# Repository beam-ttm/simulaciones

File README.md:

# Simulaciones Electromagnéticas — Proyecto CubeSat BEAM (UNLaM)

Repositorio oficial de simulaciones electromagnéticas **Full-Wave MoM (Sonnet Software 19.54)** y codiseño RF/PCB para el subsistema **ADS-B (`1090.0 MHz`, polarización circular derecha RHCP)** del CubeSat **BEAM** (Universidad Nacional de La Matanza).

---

## Estructura del Repositorio

- **[`diseno_final_patch_1090/`](diseno_final_patch_1090/)**: **Diseño final validado (Sonnet + KiCad + Imágenes para Stand)**
  - [`diseno_final_patch_1090/sonnet/`](diseno_final_patch_1090/sonnet/): Proyecto final de Sonnet (`patch_completa_jp3_gcpw_CP_1090.sonx`), parámetros Touchstone de 181 puntos (`1.000 – 1.180 GHz`, paso `1 MHz`), corrientes superficiales MoM (`sondata/.../jxy/current_1.sid`), verificación de 2 puertos de la transición coplanar-vía (`transicion_jp3_gcpw_via_50ohm.sonx`) y plantillas gráficas (`.sgrx`, `.sptx`).
  - [`diseno_final_patch_1090/kicad/`](diseno_final_patch_1090/kicad/): Proyecto de KiCad (`ads-b.kicad_pcb`, `ads-b.kicad_pro`, `ads-b.kicad_sch`, `skillkicad.md`) sincronizado 1:1 con el modelo electromagnético de Sonnet y verificado con `0` errores DRC de cobre/bordes.
  - [`diseno_final_patch_1090/imagenes_stand/`](diseno_final_patch_1090/imagenes_stand/): Infografías en alta resolución (`300 DPI` / 4K), diagramas de corriente superficial MoM, patrones de radiación 3D/Polar/2D y renders 3D raytraced listos para exhibición en stand.
- **[`sonnet/adsb_patch/`](sonnet/adsb_patch/)**: Historial de barridos paramétricos, scripts de automatización, síntesis del stackup `JLC04161H-2116` y estudios comparativos previos.

---

## Resumen de Resultados del Diseño Final (`1090.0 MHz`)

| Parámetro | Valor Simulado (Full-Wave MoM) | Especificación / Objetivo |
| :--- | :--- | :--- |
| **Frecuencia central de operación** | **`1090.0 MHz`** (mínimo en `1087.0 MHz`) | `1090.0 MHz` (ADS-B Mode-S) |
| **Pérdida de retorno $|S_{11}|$ desde `JP3`** | **`-27.62 dB`** @ `1090 MHz` (`-32.49 dB` @ `1087 MHz`) | $< -15	ext{ dB}$ |
| **Impedancia de entrada $Z_{\text{in, JP3}}$** | **`46.5 + j2.5 Ω`** @ `1090 MHz` (`49.0 + j2.1 Ω` @ `1087 MHz`) | $50\ \Omega$ |
| **Ancho de banda a `-10 dB` ($	ext{VSWR} < 2:1$)** | **`34.0 MHz`** (`1074.0 – 1108.0 MHz`) | $\ge 20	ext{ MHz}$ |
| **Ganancia Circular Derecha (`RHCP`, `E-RHP`)** | **`+9.66 dBiC`** ($\theta = 0^\circ$) | $> +6.0	ext{ dBiC}$ |
| **Rechazo Cross-Polar (`LHCP`, `E-LHP`)** | **`-5.95 dBiC`** (`15.61 dB` de aislamiento RHCP/LHCP) | $> 15	ext{ dB}$ |
| **Relación Axial (`Axial Ratio`, AR)** | **`2.90 dB`** ($\theta = 0^\circ$) | $\le 3.0	ext{ dB}$ (Polarización Circular) |
| **Ancho de haz de media potencia (`HPBW` a `-3 dB`)** | **`97.3° × 101.5°`** (`~99.4°` promedio) | Cobertura hemisférica ancha LEO |
| **Pérdida de inserción transición `JP3 -> GCPW -> Vía`** | **`|S21| = -0.049 dB`** (`|S11| = -26.85 dB`) | $< 0.1	ext{ dB}$ |

---

## Galería Visual para Stand

### 1. Excitación de Modos en Cuadratura RHCP y Patrón Cartesiano 2D

### 2. Modelo 3D Raytraced de la Placa CubeSat PC/104 (`F.Cu` Parche RHCP + `B.Cu` Front-End RF)

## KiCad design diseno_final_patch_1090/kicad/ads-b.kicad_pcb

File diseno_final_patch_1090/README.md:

# Simulaciones Electromagnéticas — Proyecto CubeSat BEAM (UNLaM)

Repositorio oficial de simulaciones electromagnéticas **Full-Wave MoM (Sonnet Software 19.54)** y codiseño RF/PCB para el subsistema **ADS-B (`1090.0 MHz`, polarización circular derecha RHCP)** del CubeSat **BEAM** (Universidad Nacional de La Matanza).

---

## Estructura del Repositorio

- **[``]()**: **Diseño final validado (Sonnet + KiCad + Imágenes para Stand)**
  - [`sonnet/`](sonnet/): Proyecto final de Sonnet (`patch_completa_jp3_gcpw_CP_1090.sonx`), parámetros Touchstone de 181 puntos (`1.000 – 1.180 GHz`, paso `1 MHz`), corrientes superficiales MoM (`sondata/.../jxy/current_1.sid`), verificación de 2 puertos de la transición coplanar-vía (`transicion_jp3_gcpw_via_50ohm.sonx`) y plantillas gráficas (`.sgrx`, `.sptx`).
  - [`kicad/`](kicad/): Proyecto de KiCad (`ads-b.kicad_pcb`, `ads-b.kicad_pro`, `ads-b.kicad_sch`, `skillkicad.md`) sincronizado 1:1 con el modelo electromagnético de Sonnet y verificado con `0` errores DRC de cobre/bordes.
  - [`imagenes_stand/`](imagenes_stand/): Infografías en alta resolución (`300 DPI` / 4K), diagramas de corriente superficial MoM, patrones de radiación 3D/Polar/2D y renders 3D raytraced listos para exhibición en stand.
- **[`sonnet/adsb_patch/`](sonnet/adsb_patch/)**: Historial de barridos paramétricos, scripts de automatización, síntesis del stackup `JLC04161H-2116` y estudios comparativos previos.

---

## Resumen de Resultados del Diseño Final (`1090.0 MHz`)

| Parámetro | Valor Simulado (Full-Wave MoM) | Especificación / Objetivo |
| :--- | :--- | :--- |
| **Frecuencia central de operación** | **`1090.0 MHz`** (mínimo en `1087.0 MHz`) | `1090.0 MHz` (ADS-B Mode-S) |
| **Pérdida de retorno $|S_{11}|$ desde `JP3`** | **`-27.62 dB`** @ `1090 MHz` (`-32.49 dB` @ `1087 MHz`) | $< -15	ext{ dB}$ |
| **Impedancia de entrada $Z_{\text{in, JP3}}$** | **`46.5 + j2.5 Ω`** @ `1090 MHz` (`49.0 + j2.1 Ω` @ `1087 MHz`) | $50\ \Omega$ |
| **Ancho de banda a `-10 dB` ($	ext{VSWR} < 2:1$)** | **`34.0 MHz`** (`1074.0 – 1108.0 MHz`) | $\ge 20	ext{ MHz}$ |
| **Ganancia Circular Derecha (`RHCP`, `E-RHP`)** | **`+9.66 dBiC`** ($\theta = 0^\circ$) | $> +6.0	ext{ dBiC}$ |
| **Rechazo Cross-Polar (`LHCP`, `E-LHP`)** | **`-5.95 dBiC`** (`15.61 dB` de aislamiento RHCP/LHCP) | $> 15	ext{ dB}$ |
| **Relación Axial (`Axial Ratio`, AR)** | **`2.90 dB`** ($\theta = 0^\circ$) | $\le 3.0	ext{ dB}$ (Polarización Circular) |
| **Ancho de haz de media potencia (`HPBW` a `-3 dB`)** | **`97.3° × 101.5°`** (`~99.4°` promedio) | Cobertura hemisférica ancha LEO |
| **Pérdida de inserción transición `JP3 -> GCPW -> Vía`** | **`|S21| = -0.049 dB`** (`|S11| = -26.85 dB`) | $< 0.1	ext{ dB}$ |

---

## Galería Visual para Stand

### 1. Excitación de Modos en Cuadratura RHCP y Patrón Cartesiano 2D

### 2. Modelo 3D Raytraced de la Placa CubeSat PC/104 (`F.Cu` Parche RHCP + `B.Cu` Front-End RF)

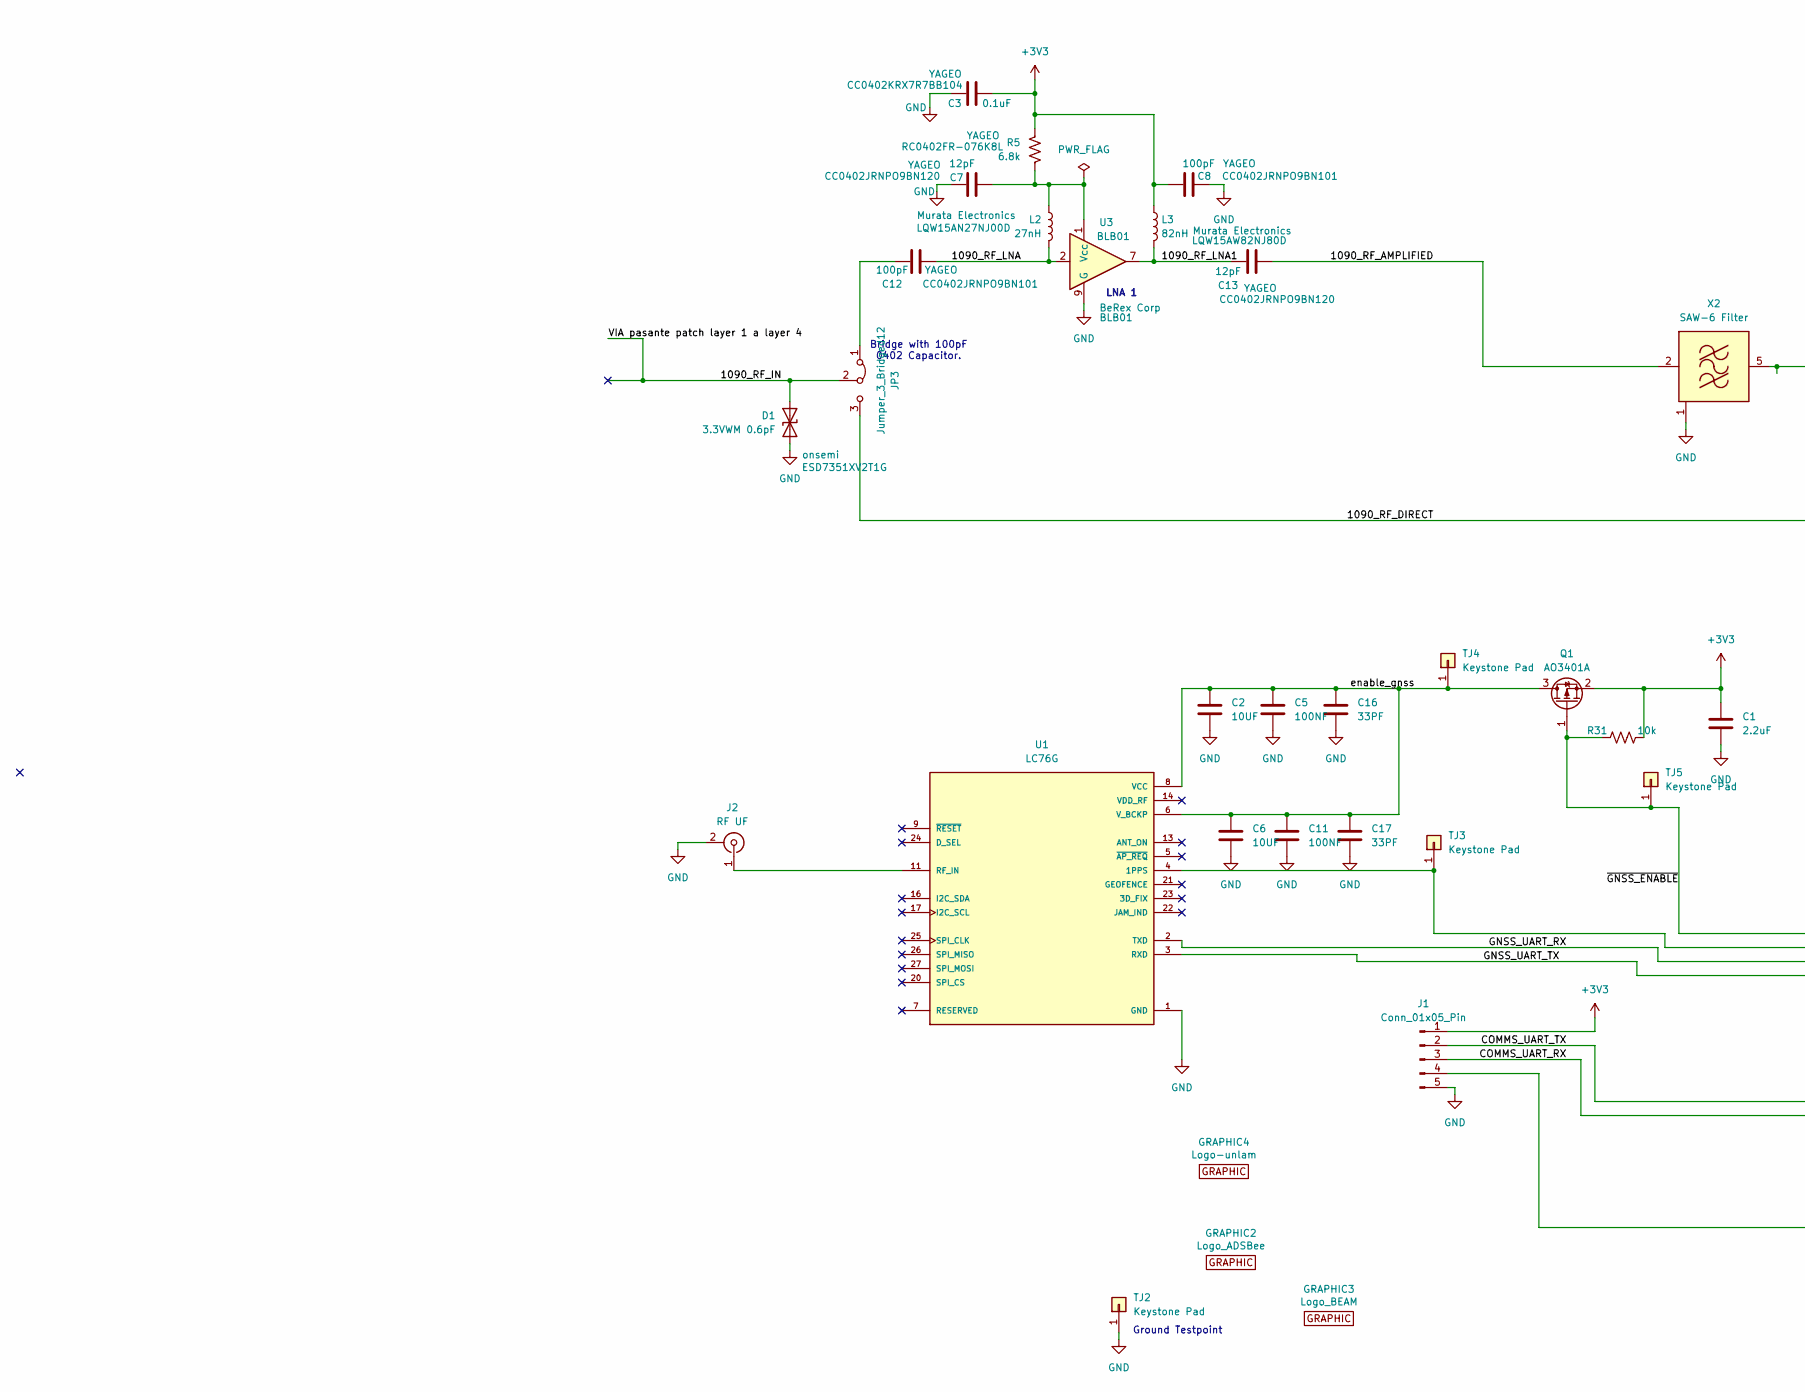
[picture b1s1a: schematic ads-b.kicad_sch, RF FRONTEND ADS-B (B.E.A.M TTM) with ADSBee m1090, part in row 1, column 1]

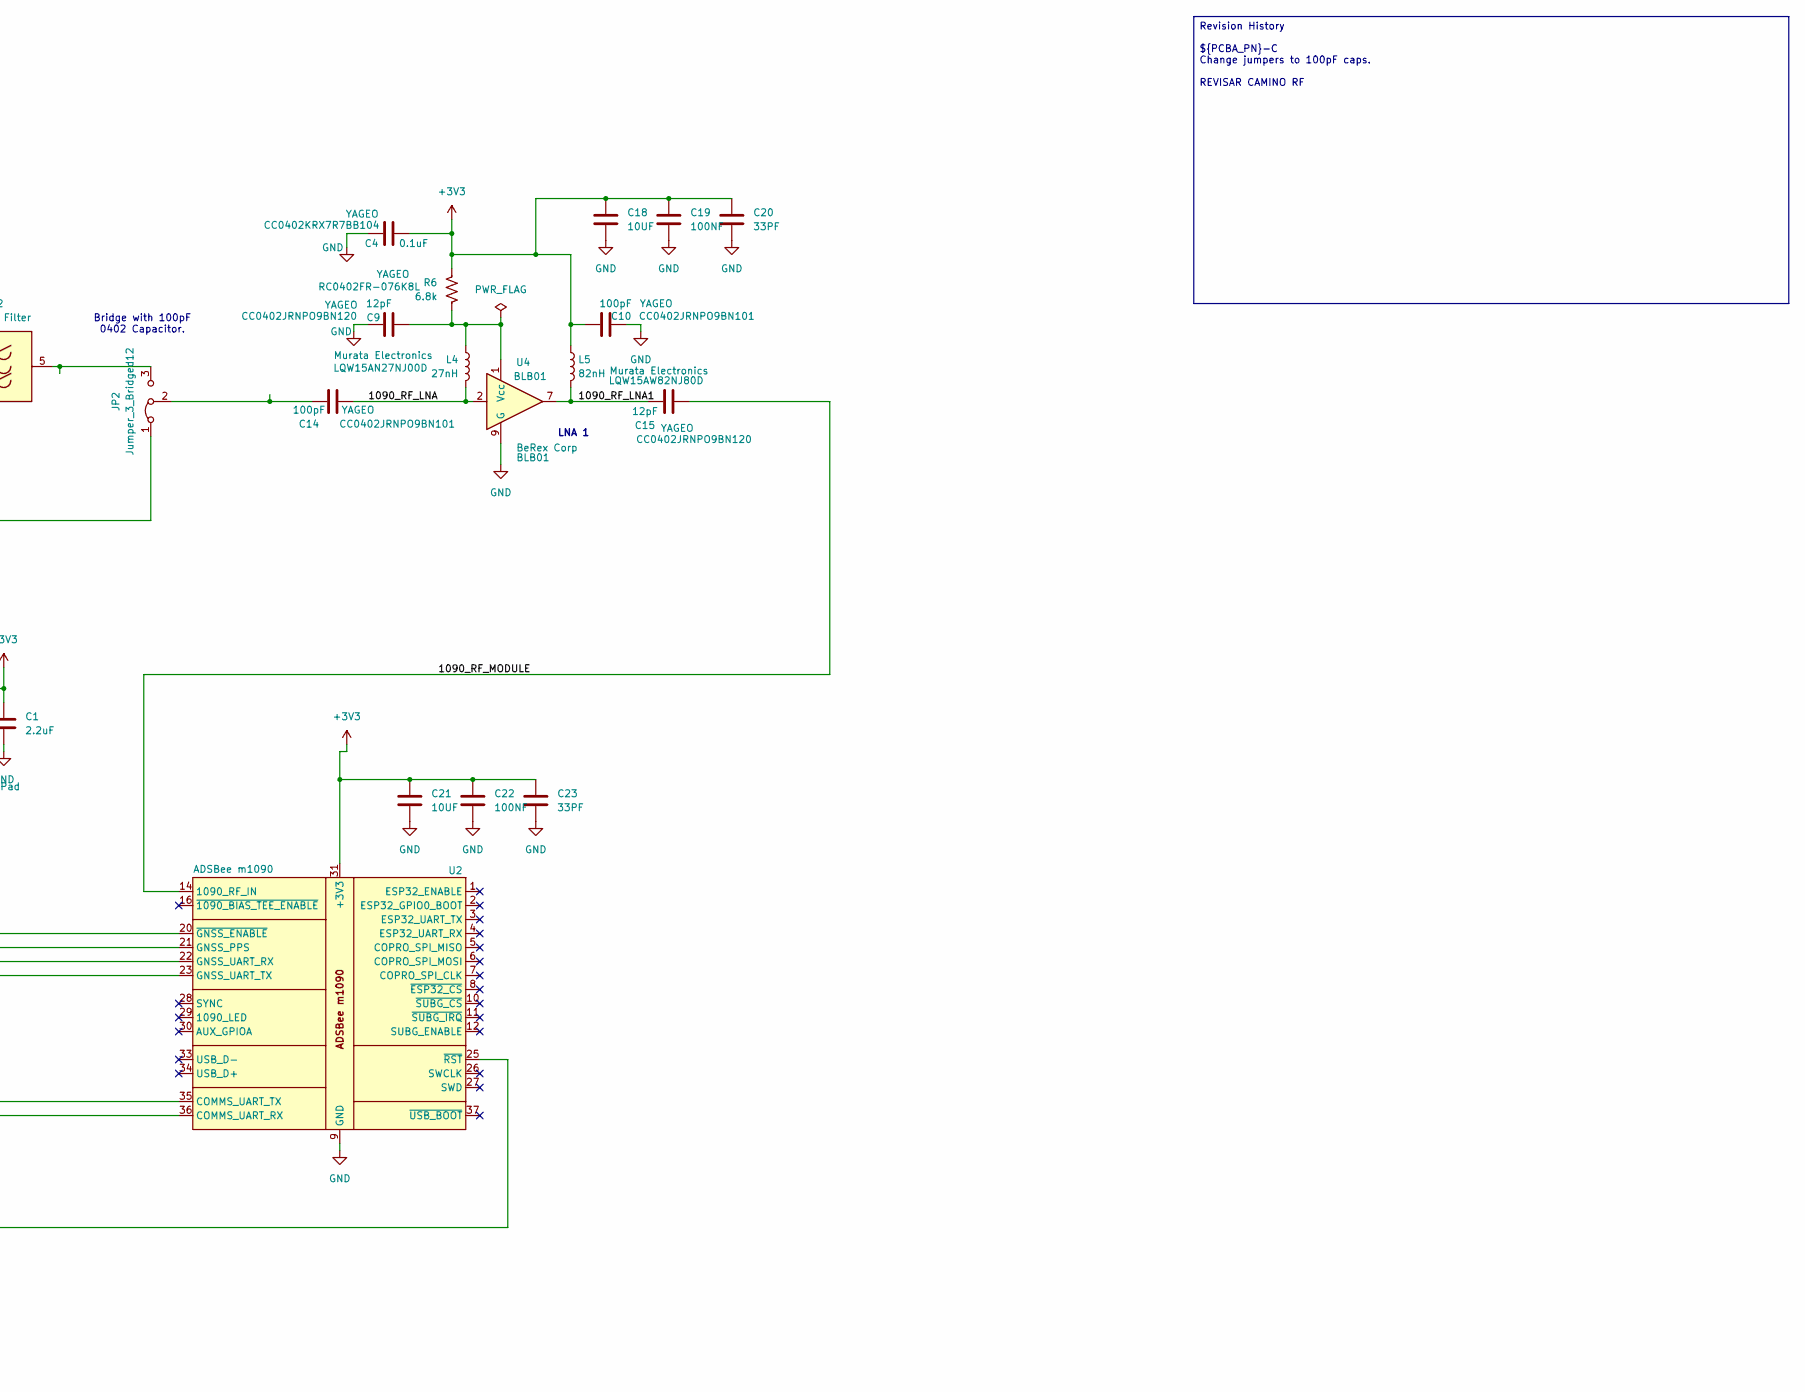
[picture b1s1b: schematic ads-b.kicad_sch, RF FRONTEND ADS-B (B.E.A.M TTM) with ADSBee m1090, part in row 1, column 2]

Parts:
C1: 2.2uF; C_0603_1608Metric; Voltage 10V; MPN CL10B225KP8NNNC
C2, C6, C18, C21: 10UF; C_0603_1608Metric
C3, C4: 0.1uF; C_0402_1005Metric; Voltage 16V; Tolerance 10%; MPN CC0402KRX7R7BB104; LCSC PN C60474
C5, C11, C19, C22: 100NF; C_0603_1608Metric
C7, C9, C13, C15: 12pF; C_0402_1005Metric; Voltage 50V; Tolerance 5%; MPN CC0402JRNPO9BN120; LCSC PN C326662
C8, C10, C12, C14: 100pF; C_0402_1005Metric; Voltage 50V; Tolerance 5%; MPN CC0402JRNPO9BN101; LCSC PN C106200
C16, C17, C20, C23: 33PF; C_0603_1608Metric
D1: 3.3VWM 0.6pF; D_SOD-523; MPN ESD7351XV2T1G; LCSC PN C2912559
GRAPHIC2: Logo_ADSBee; ADSBeelogo
GRAPHIC3: Logo_BEAM; BEAM_logo_22.4mm
GRAPHIC4: Logo-unlam; ADSBeelogo
J1: Conn_01x05_Pin; JST_SH_SM05B-SRSS-TB_1x05-1MP_P1.00mm_Horizontal
J2: RF UF; U.FL_Hirose_U.FL-R-SMT-1_Vertical
JP2, JP3: Jumper_3_Bridged12; Jumper_C_0402_3Pole_Bridged12_3Down; MPN CC0402JRNPO9BN101; LCSC PN C106200
L2, L4: 27nH; L_0402_1005Metric; Tolerance 5%; MPN LQW15AN27NJ00D; LCSC PN C113112
L3, L5: 82nH; L_0402_1005Metric; Tolerance 5%; MPN LQW15AW82NJ80D; LCSC PN C3222285
Q1: AO3401A; SOT-23
R5, R6: 6.8k; R_0402_1005Metric; Tolerance 1%; MPN RC0402FR-076K8L; LCSC PN C93940
R31: 10k; R_0402_1005Metric; Tolerance 1%; MPN RC0402FR-0710KL; LCSC PN C60490
TJ2, TJ3, TJ4, TJ5: Keystone Pad; TestPoint_Pad_1.0x1.0mm; MPN 5015; LCSC PN C2906768
U1: LC76G; XCVR_LC76G; PARTREV 1.0
U2: ADSBee m1090; PantsForBirds_ADSBee_m1090_Module
U3, U4: BLB01; Berex_DFN-8-1EP_2x2mm_P0.5mm_SmallPadWithDots; MPN BLB01
X2: SAW-6 Filter; Filter_SAW-6_3.0x3.0mm

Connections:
+3V3: C1.1, C3.1, C4.1, C8.1, C10.1, C18.1, C19.1, C20.1, C21.1, C22.1, C23.1, J1.1, L3.1, L5.1, Q1.2 (S), R5.1, R6.1, R31.2, U2.31 (+3V3)
/1090_RF_AMPLIFIED: C13.2, X2.2 (IN)
/1090_RF_DIRECT: JP2.1 (A), JP3.3 (B)
/1090_RF_IN: D1.1 (A1), JP3.2 (C)
/1090_RF_LNA: C12.2, C14.2, L2.2, L4.2, U3.2, U4.2
/1090_RF_LNA1: C13.1, C15.1, L3.2, L5.2, U3.7, U4.7
/1090_RF_MODULE: C15.2, U2.14 (1090_RF_IN)
/COMMS_UART_RX: J1.3, U2.36 (COMMS_UART_RX)
/COMMS_UART_TX: J1.2, U2.35 (COMMS_UART_TX)
/GNSS_UART_RX: U1.2 (TXD), U2.22 (GNSS_UART_RX)
/GNSS_UART_TX: U1.3 (RXD), U2.23 (GNSS_UART_TX)
/enable_gnss: C2.1, C5.1, C6.1, C11.1, C16.1, C17.1, Q1.3 (D), TJ4.1 (Pin_1_1), U1.6 (V_BCKP), U1.8 (VCC)
/~GNSS_ENABLE: Q1.1 (G), R31.1, TJ5.1 (Pin_1_1), U2.20 (~GNSS_ENABLE)
GND: C1.2, C2.2, C3.2, C4.2, C5.2, C6.2, C7.1, C8.2, C9.1, C10.2, C11.2, C16.2, C17.2, C18.2, C19.2, C20.2, C21.2, C22.2, C23.2, D1.2 (A2), J1.5, J2.2 (Ext), TJ2.1 (Pin_1_1), U1.1 (GND), U1.10 (GND), U1.12 (GND), U1.28 (GND), U2.9 (GND), U2.13 (GND), U2.15 (GND), U2.17 (GND), U2.18 (GND), U2.19 (GND), U2.24 (GND), U2.32 (GND), U2.38 (GND), U3.9 (G), U4.9 (G), X2.1 (GND), X2.3 (GND), X2.4 (GND), X2.6 (GND)
unnamed: J1.4, U2.25 (~RST)
unnamed: J2.1 (In), U1.11 (RF_IN)
unnamed: JP2.3 (B), X2.5 (OUT)
unnamed: C14.1, JP2.2 (C)
unnamed: C12.1, JP3.1 (A)
unnamed: TJ3.1 (Pin_1_1), U1.4 (1PPS), U2.21 (GNSS_PPS)
unnamed: C7.2, L2.1, R5.2, U3.1 (Vcc)
unnamed: C9.2, L4.1, R6.2, U4.1 (Vcc)

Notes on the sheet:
Bridge with 100pF 0402 Capacitor.
LNA 1
Ground Testpoint
Revision History ${PCBA_PN}-C Change jumpers to 100pF caps. REVISAR CAMINO RF

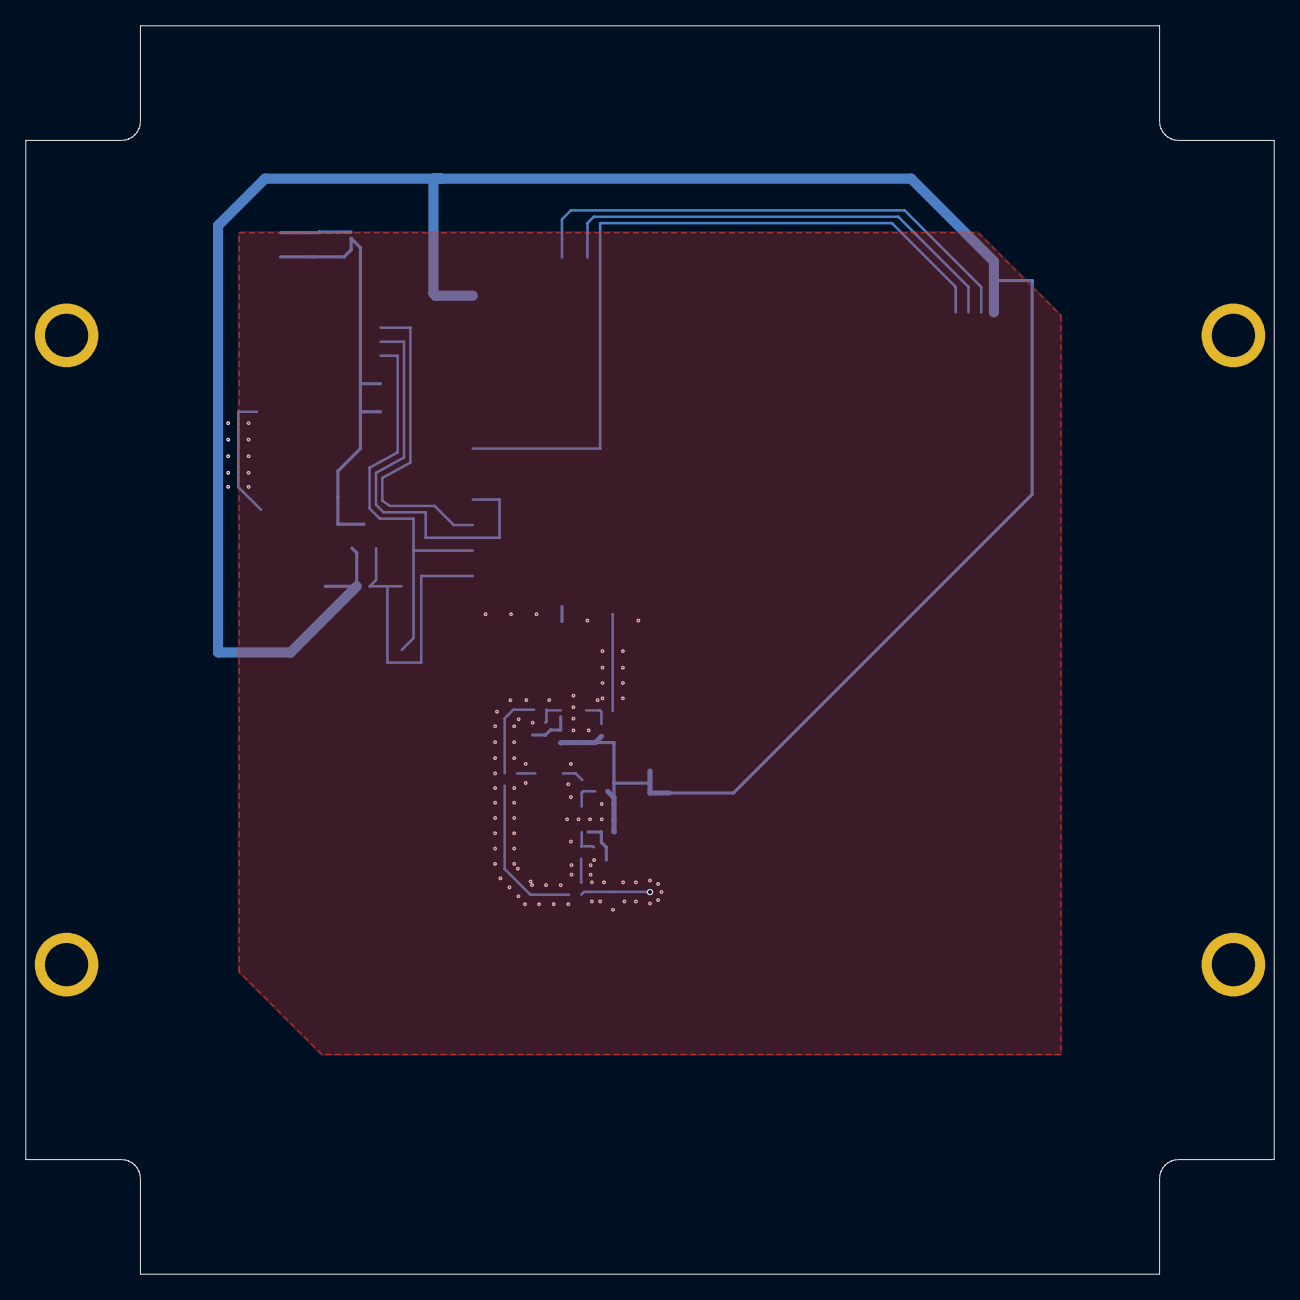
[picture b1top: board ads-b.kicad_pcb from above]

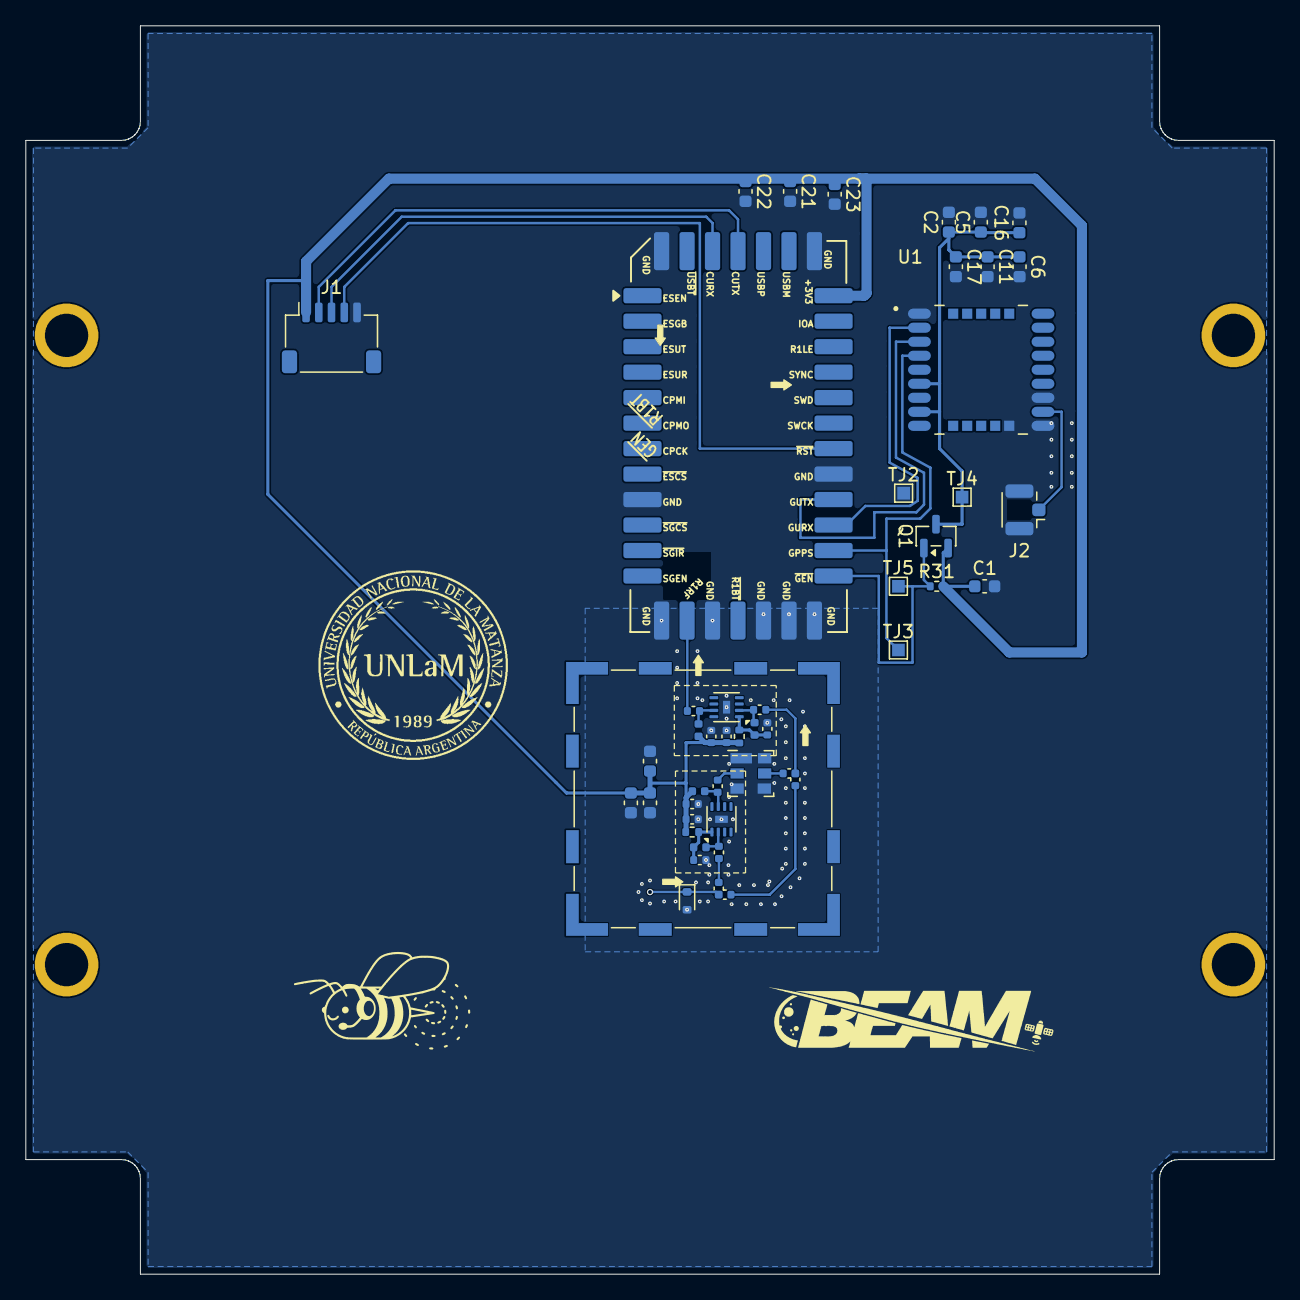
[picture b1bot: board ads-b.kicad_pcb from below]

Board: 4 copper layers, 98.0 x 98.0 mm, 48 parts (48 on the bottom side), 22 nets.
